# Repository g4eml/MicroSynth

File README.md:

# MicroSynth
## A Tiny  160 MHz to 1297 MHz RF Synthesiser Module using the CMT2119A Chip.

## Description
The CMT2119A chip is designed as a low cost remote control transmitter operating between 240 and 960 MHz. It is software programmable and has an onboard EEPROM to store its settings. As such it can operate without a separate microcontroller and only needs a 26 MHz reference Crystal and output matching components. 
The datasheet states that the device can be programmed to operate on any frequency between 240 MHz and 960 MHz, some experimenting has shown that in practice this can be extended to aproximately 160MHz and 1297 MHz although this range may vary between chips. Some reverse engineering was done to determine the exact programming sequence needed, this is detailed in this document https://github.com/g4eml/MicroSynth/blob/main/Documents/CMT2119A%20Programming%20Notes.pdf . 

## Construction
Full schematics and PCB design are included in this repository. The CMT2119A devices are available from AliExpress. The NT3225SA 26.000 Mhz TCXO can be found from many suppliers. The remaining components are not critical. 

## Programming

Programming of the CMT2119A chip is done using a RP2040 Zero module which can be created as follows:-

1. Locate the latest compiled firmware file 'MicroSynth.uf2' which will be found here https://github.com/g4eml/MicroSynth/releases and save it to your desktop. 

2. Hold down the BOOTSEL button on the RP2040 module while connecting it to your PC using its USB port. The RP2040 should appear as a USB disk drive on your PC.

3. Copy the .uf2 file onto the USB drive. The RP2040 will recognise the file and immediately update its firmware and reboot.

4. Windows 10 and above should automatically load the necessary driver and allocate a Com Port to the RP2040.

To enter programming mode you need to connect to the USB serial port using a terminal program such as Putty or Terraterm. Pressing any key should result in the menu being displayed.

### Connections for programming

| RP2040 | CMT2119A |
| :---:  |  :---:   |
|3V3     |   VDD    |
|GND     |   GND    |
|GPO6    |  DATA    | 
|GPO7    |   CLK    | 

The Arduino Sketch is also included in this repository if you need to make any changes. 

More comprehensive control of the CMT2119A can also be done by using my RP2040_Synth Programmer which can be found here https://github.com/g4eml/RP2040_Synth .

## Tuning
The matching components may need to be selected for optimum output on your desired frequency according to the table in the schematic. Populating with the 'Wideband' components will work for any frequency but the output will contain harmonics as it is a square wave.
Ouput power in the 'Wideband' configuration ranges from approx +13 dBm at 160 MHz to approx 0dBm at 1296 MHz.

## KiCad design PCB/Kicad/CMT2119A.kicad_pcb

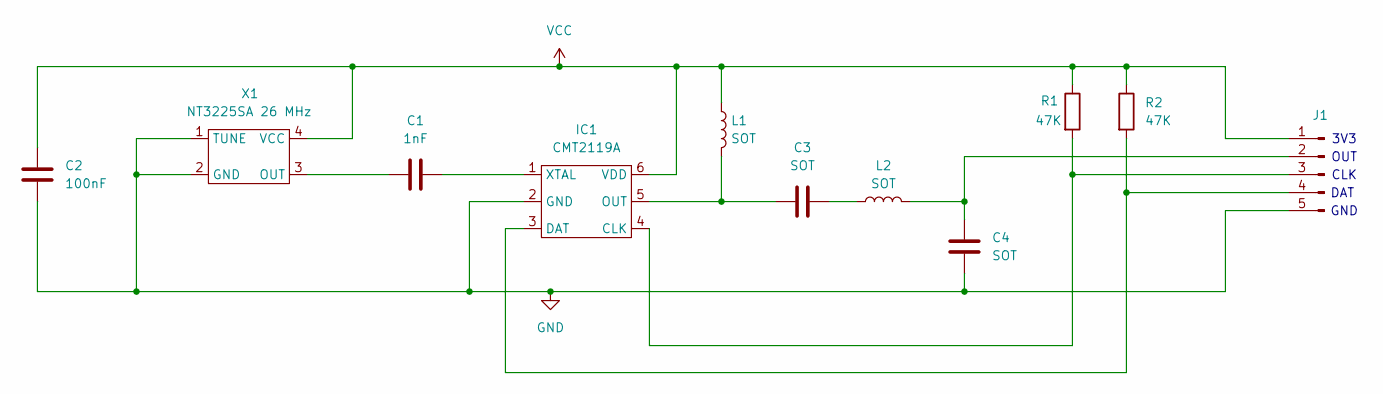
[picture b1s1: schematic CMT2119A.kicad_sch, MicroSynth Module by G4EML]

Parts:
C1: 1nF; C_0805_2012Metric
C2: 100nF; C_0805_2012Metric
C3, C4: SOT; C_0805_2012Metric
IC1: CMT2119A; SOT-23-6
J1: Conn_01x05_Pin; PinHeader_1x05_P2.54mm_Vertical
L1, L2: SOT; L_0805_2012Metric
R1, R2: 47K; R_0805_2012Metric
X1: NT3225SA 26 MHz; Crystal_SMD_3225-4Pin_3.2x2.5mm

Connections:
GND: C2.2, C4.2, IC1.2 (GND), J1.5, X1.1 (TUNE), X1.2 (GND)
unnamed: C3.2, L2.1
unnamed: IC1.4 (CLK), J1.3, R1.2
unnamed: IC1.3 (DAT), J1.4, R2.2
unnamed: C3.1, IC1.5 (OUT), L1.2
unnamed: C1.2, IC1.1 (XTAL)
unnamed: C4.1, J1.2, L2.2
unnamed: C1.1, X1.3 (OUT)
VCC: C2.1, IC1.6 (VDD), J1.1, L1.1, R1.1, R2.1, X1.4 (VCC)

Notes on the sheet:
CLK
3V3
DAT
OUT
GND

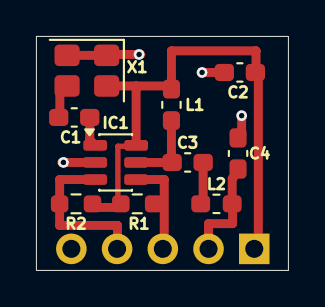
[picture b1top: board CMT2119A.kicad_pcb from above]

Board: 2 copper layers, 14.0 x 13.0 mm, 11 parts (0 on the bottom side), 9 nets.

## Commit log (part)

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2026-04-15 Enhance README with detailed module information
    Expanded the README to include detailed descriptions of the module, construction, programming, and tuning.
2026-04-15 Update README with programming notes link
    Added a link to the programming notes document for the CMT2119A chip.
2026-04-15 Fix typos in README.md
2026-04-15 Fix link to programming notes document
    Updated the link to the CMT2119A programming notes document from .odt to .pdf.
2026-04-15 Rename CMT2119A Programming Notes.pdf to Documents/CMT2119A Programming Notes.pdf
